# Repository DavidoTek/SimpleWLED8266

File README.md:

# SimpleWLED8266

SimpleWLED8266 is a simple, ESP8266-based, and WLED-powered LED controller board, supporting both analog and digital LED strips. The board features AO3400 mosfets to drive the analog LEDs and uses the 74AHCT125 buffer as a level-shifter for the digital LEDs which require 5V.

The board is very simple to solder since it only features a few parts and the smallest SMD part is of the size 0805. It does not use a switching regulator, reducing complexity and noise, but also decreasing the efficiency of the board. Make sure to pick 1117 regulators that support input voltages >12V! (e.g., LM1117 by TI)

The recommended software is [WLED](https://github.com/WLED/WLED), but other software like [ESPHome](https://esphome.io/) or [Tasmota](https://github.com/arendst/Tasmota) can also be used. Check out [this page](https://kno.wled.ge/basics/compatible-led-strips/) for a list of LED strips supported by WLED.

Disclaimer: This was made as a hobby project, so errors in the design are possible. Handle high voltages with care and do not overload the PCB since it can overheat and cause a fire. Please report problems in the design!

## Content

File/Folder                       | Description
----------------------------------|-------------------------------
simplewled8266/                   | KiCad project for the PCB
SimpleWLED8266_Case_Bottom.stl    | 3D-printable case (bottom)
SimpleWLED8266_Case_Bottom_ScrewMount.stl    | 3D-printable case (bottom, with screw mounts)
SimpleWLED8266_Case_Top.stl       | 3D-printable case (top)
SimpleWLED8266_Label.pdf          | Label for the 3D-printed case

## Wiring

The following GPIO functions need to be configured in WLED:

GPIO        | Function
------------|----------------------
12          | Red (analog)
5           | Green (analog)
14          | Blue (analog)
2           | Data (digital)
13          | Clock (digital)
0           | Button

## BOM

Quantity | Type       | Value       | Description
---------|------------|-------------|-------------------------------------
7        | Capacitor  | 100n        | Decoupling capacitors
1        | Capacitor  | 10u         | Capacitor
1        | Capacitor  | 470u        | Capacitor
1        | Fuse       | Fuse        | Fuse
1        | Connector  | PWR         | 
1        | Connector  | LEDs        | 
1        | Connector  | PROG        | 
3        | MOSFET     | AO3400A     | N-channel MOSFET for analog LEDs
2        | Resistor   | 62          | Between level-shifter and LEDs
8        | Resistor   | 10k         | Pull-up / pull-down resistors
1        | Switch     | SW_Push     | 
1        | Module     | ESP-12F     | ESP8266
1        | Buffer     | 74AHCT125   | Buffer as level-shifter to 5V
1        | Regulator  | AMS1117-5.0 | 5V linear regulator, Vin>=12V
1        | Regulator  | AMS1117-3.3 | 3.3V linear regulator, Vin>=12V

## Photos

Source of the WLED logo: https://github.com/wled/WLED/blob/main/images/wled_logo_akemi.png

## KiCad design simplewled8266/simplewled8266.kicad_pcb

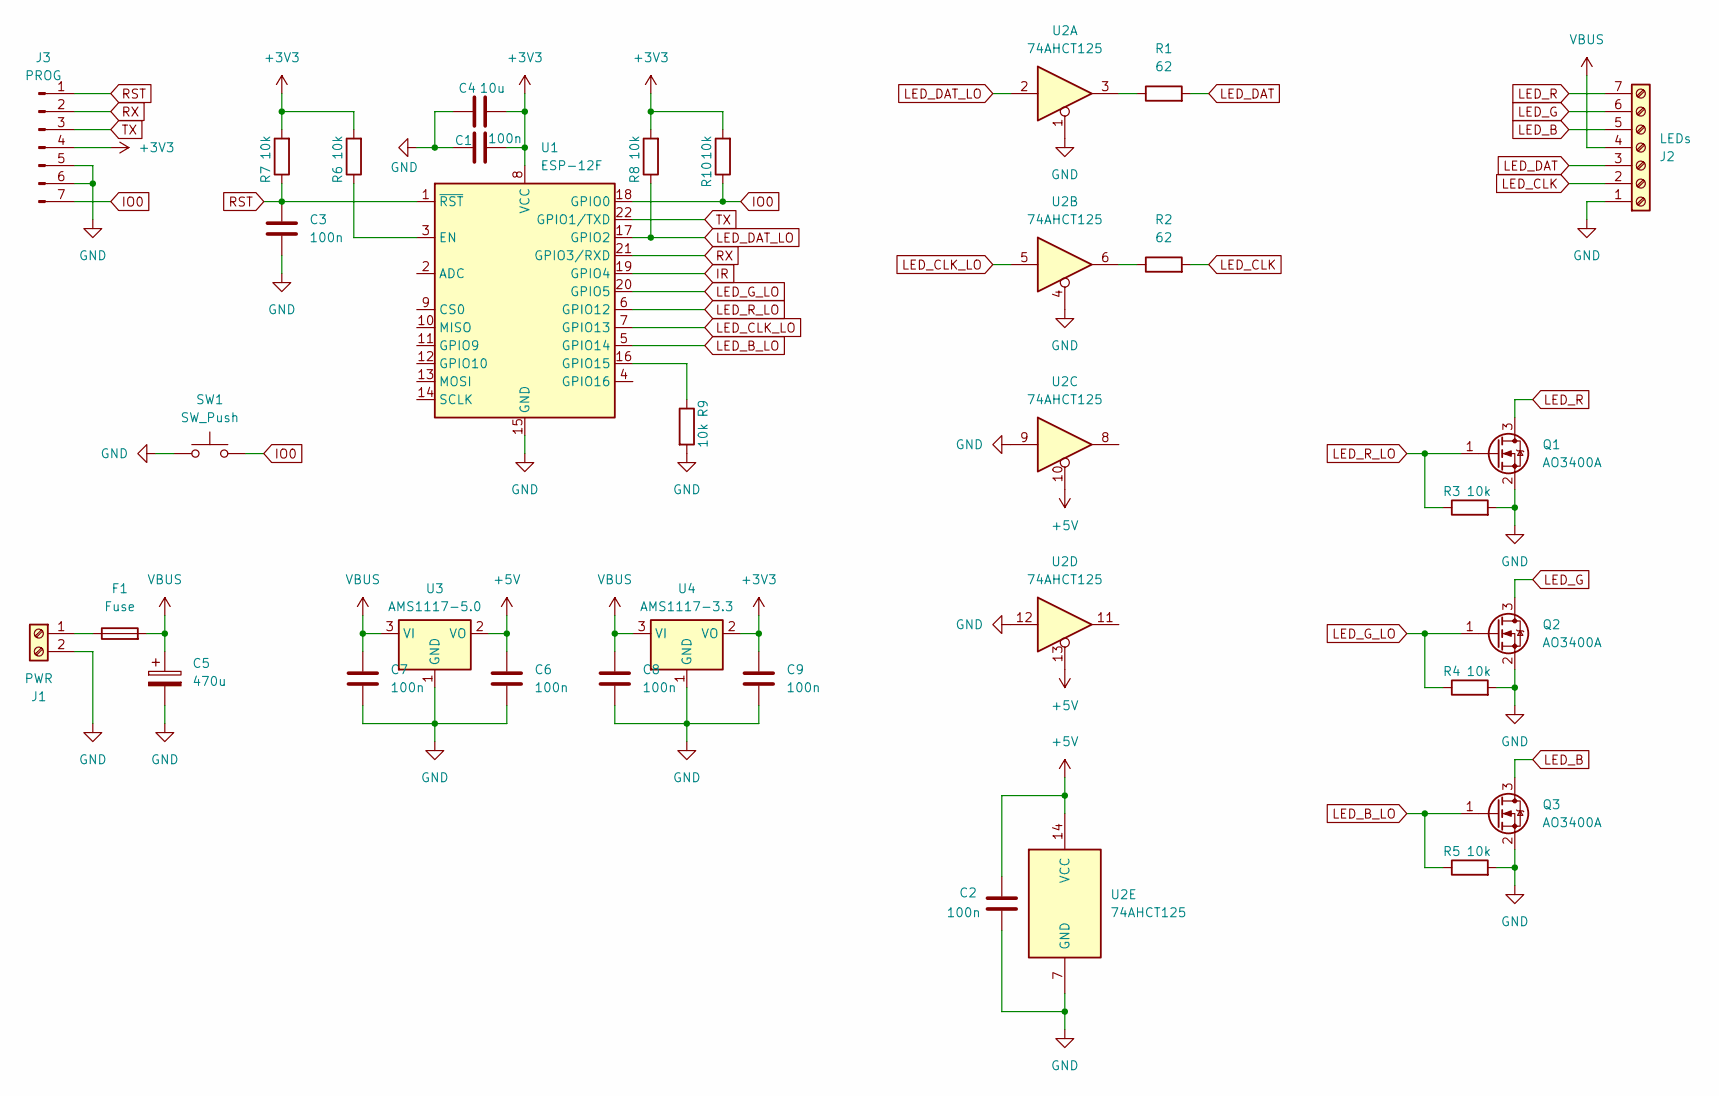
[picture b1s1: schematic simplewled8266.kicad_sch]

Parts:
C1, C2, C3, C6, C7, C8, C9: 100n; C_0805_2012Metric_Pad1.18x1.45mm_HandSolder
C4: 10u; C_0805_2012Metric_Pad1.18x1.45mm_HandSolder
C5: 470u; CP_Radial_D10.0mm_P5.00mm
F1: Fuse; Fuse_Blade_Mini_directSolder
J1: PWR; TerminalBlock_Phoenix_MKDS-1,5-2-5.08_1x02_P5.08mm_Horizont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
J2: LEDs; TerminalBlock_Phoenix_MKDS-1,5-7-5.08_1x07_P5.08mm_Horizont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
J3: PROG; PinHeader_1x07_P2.54mm_Vertical
Q1, Q2, Q3: AO3400A; SOT-23
R1, R2: 62; R_0805_2012Metric_Pad1.20x1.40mm_HandSolder
R3, R4, R5, R6, R7, R8, R9, R10: 10k; R_0805_2012Metric_Pad1.20x1.40mm_HandSolder
SW1: SW_Push; SW_PUSH_6mm
U1: ESP-12F; ESP-12E
U2: 74AHCT125; SOIC-14_3.9x8.7mm_P1.27mm
U3: AMS1117-5.0; SOT-223-3_TabPin2
U4: AMS1117-3.3; SOT-223-3_TabPin2

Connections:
+3V3: C1.2, C4.2, C9.1, J3.4, R6.2, R7.2, R8.2, R10.2, U1.8 (VCC), U4.2 (VO)
+5V: C2.1, C6.1, U2.10, U2.13, U2.14 (VCC), U3.2 (VO)
GND: C1.1, C2.2, C3.2, C4.1, C5.2, C6.2, C7.2, C8.2, C9.2, J1.2, J2.1, J3.5, J3.6, Q1.2 (S), Q2.2 (S), Q3.2 (S), R3.2, R4.2, R5.2, R9.2, SW1.1, U1.15 (GND), U2.1, U2.4, U2.7 (GND), U2.9, U2.12, U3.1 (GND), U4.1 (GND)
IO0: J3.7, R10.1, SW1.2, U1.18 (GPIO0)
IR: U1.19 (GPIO4)
LED_B: J2.5, Q3.3 (D)
LED_B_LO: Q3.1 (G), R5.1, U1.5 (GPIO14)
LED_CLK: J2.2, R2.2
LED_CLK_LO: U1.7 (GPIO13), U2.5
LED_DAT: J2.3, R1.2
LED_DAT_LO: R8.1, U1.17 (GPIO2), U2.2
LED_G: J2.6, Q2.3 (D)
LED_G_LO: Q2.1 (G), R4.1, U1.20 (GPIO5)
LED_R: J2.7, Q1.3 (D)
LED_R_LO: Q1.1 (G), R3.1, U1.6 (GPIO12)
unnamed: F1.1, J1.1
unnamed: R1.1, U2.3
unnamed: R2.1, U2.6
unnamed: R6.1, U1.3 (EN)
unnamed: R9.1, U1.16 (GPIO15)
RST: C3.1, J3.1, R7.1, U1.1 (~RST)
RX: J3.2, U1.21 (GPIO3/RXD)
TX: J3.3, U1.22 (GPIO1/TXD)
VBUS: C5.1, C7.1, C8.1, F1.2, J2.4, U3.3 (VI), U4.3 (VI)

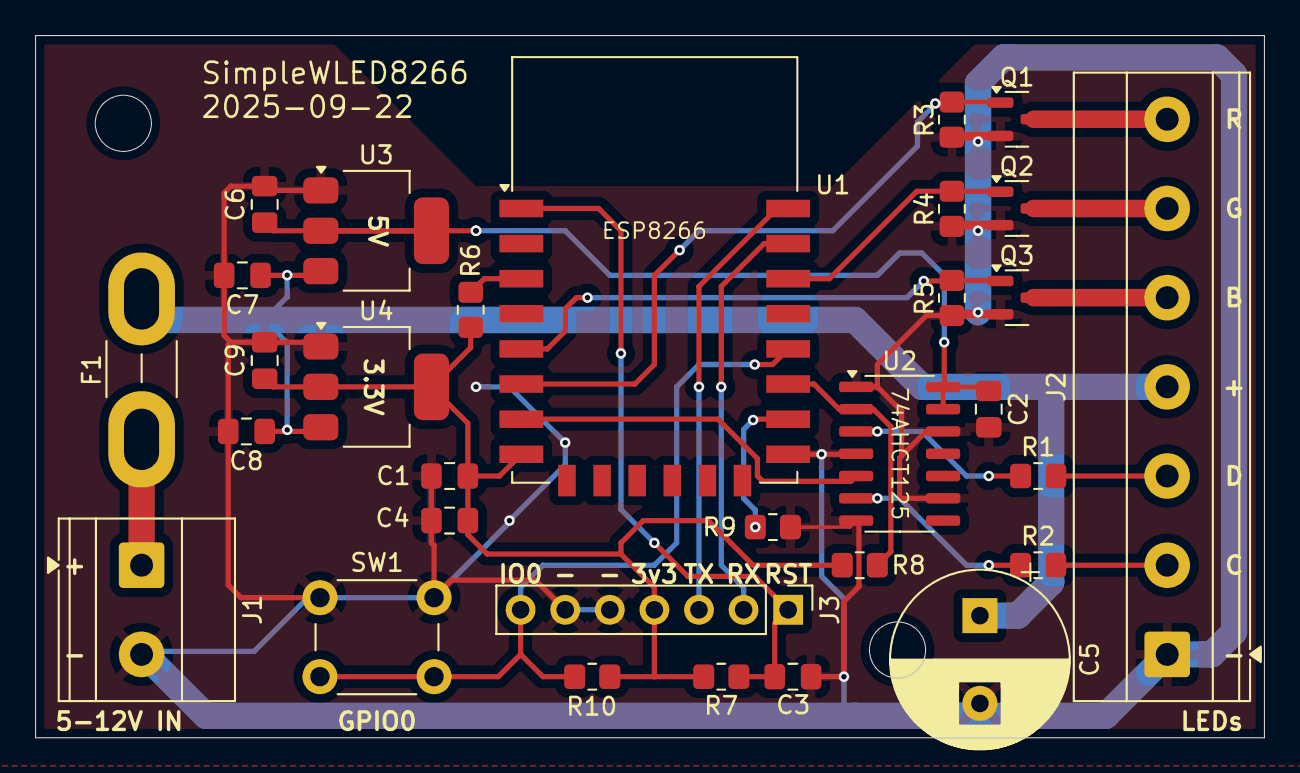
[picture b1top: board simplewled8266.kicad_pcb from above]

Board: 2 copper layers, 70.0 x 40.0 mm, 31 parts (0 on the bottom side), 23 nets.

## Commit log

2025-10-07 Add SimpleWLED8266_Case_Bottom_ScrewMount.stl
